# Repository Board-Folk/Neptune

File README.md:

# Neptune 32X/MD2

The Sega Neptune was an unreleased console that would have been a stand-alone 32X.
This project provides a PCB that combines the 32X and Mega Drive/Genesis 2 that fits
in an original Mega Drive/Genesis 2 case or the reimagined Neptune case designed by
DVIZIX.

[![Promo video][PromoVideoThumbnail]][PromoVideo]

**NOTE**: In order to use these PCBs successfully you will need to be proficient in:

* Soldering-fine pitched surface mount components.
* In most cases, desoldering said components to obtain these from a donor board.
* Troubleshooting any issues that may arise.

Development and testing of these PCBs has shown that successfully assembling a
working board is challenging even for skilled, experienced builders. Please read the
build notes below carefully before starting. If you are in any doubt, it is highly
recommended to enlist the help of someone with a known track record.

The authors are not obliged to provide support, nor shall they be held responsible
for botched attempts at using these boards. Should you however find a legitimate flaw
in the board's design or have suggestions for improvements, please feel free to
submit an issue.

## Errata

When using anything other than the latest release, check against this table if there
are any outstanding fixes that should be applied to your particular board revision.

| Issue          | Description                          | Affected Revisions  | Service Bulletin           |
|----------------|--------------------------------------|---------------------|----------------------------|
| [#3][Issue3]   | Region/version register instability. | <= r1.3 (Sept 2024) | [CSB_NEP_001][CSB_NEP_001] |
| -              | Black screen after power-on reset.   | <= r1.3 (Sept 2024) | [CSB_NEP_002][CSB_NEP_002] |

[Issue3]: https://github.com/Board-Folk/Neptune/issues/3
[CSB_NEP_001]: https://raw.githubusercontent.com/Board-Folk/Neptune/master/service/CSB_NEP_001.pdf
[CSB_NEP_002]: https://raw.githubusercontent.com/Board-Folk/Neptune/master/service/CSB_NEP_002.pdf

## Features and Limitations

* Fits original Mega Drive 2 (PAL), Genesis 2 or DVIZIX Neptune cases. Separate
  power/reset switch locations are provided for each (see the `stl` directory for
  files with which to 3D print spacers for the buttons if using the DVIZIX case).
* NOT compatible with the Japanese Mega Drive 2 case due to this using a sliding
  power switch with a different footprint to that of the push button style.
* Modern power circuit by Zaxour (requires 9V DC PSU rated for at least 1A).
* Integrated switchless region mod using PIC16F630 or compatible.
* Integrated "Triple Bypass" mod for improved RGB and audio.
* Provisional support for Sega Master System games via integrated mod by DogP.\*
* Compatible with the original Sega CD/Mega CD.\*\*
* Not compatible with flash cart-based Sega CD/Mega CD implementations such as
  the Mega EverDrive Pro. The Mega SD does how ever work when used in combination
  with the MSDEXP expansion port adapter (thanks to Bob from [RetroRGB](https://www.retrorgb.com/)
  for [testing this live][RetroRGBCDVideo]).
* As the 32X hardware is integrated into the design, there is NO way to disable this.
* No mono audio output.
* No Dual Frequency Oscillator (DFO) is built in but, should you opt to install
  one that fits in the original oscillator footprint, a pad for the PAL/NTSC
  switching signal is provided close by.

\* Master System compatibility is not extensively tested. Original cartridges have
been shown to work when using simple pass-through adapters. Using Mega Drive flash
carts to run Master System games may or may not work. Some such cartridges check for
the presence of a 32X and, if detected, will refuse to boot in Master System mode,
as this would usually cause a hardware conflict. In some cases this check can be
disabled in the flash cart's menu. While we believe that this is safe, you do so at
your own risk.

\*\* The model 2 Sega CD/Mega CD uses the +9V pin on the expansion connector to power
itself on along with the attached console. This board does not however provide 9V
to this pin. Testing has shown that the CD hardware will also power on with only 5V
on this pin. We're not aware of any add-ons that require 9V on the expansion connector,
so what would usually be +9V is connected to +5V by a trace between the pads near
B26 and B28. If you do however really need it, there is another +9V pad near the
power jack. This is however not switched along with the console and will remain
powered as long as there is power to the jack. You could rig up something with
a transistor or MOSFET to make 9V switch on along with the console. Of course, making
any such modification will require the trace between +5V and +9V be cut.

## PCB Production

**NOTE**: it is highly discouraged to have boards manufactured based on the current
state of the master branch or indeed any commit other than those tagged as actual
[releases][Releases]. Any other commits may contain errors or half-finished features
and using them limits the ability of others to provide support due to the unknown
state of the boards.

Minimum track widths, clearances and via sizes are within the standard
offering of modern PCB fabricators. Gerber files are generated with the relevant
options for [JLCPCB](https://jlcpcb.com/) (included in the "Assets" section of
the individual [releases][Releases]). Placeholders for the order number are
provided so remember to select the "Specify location" option for this when ordering.
If using another service you may wish to remove or replace this placeholder.
If using PCBWay, please consider using this [shared project][PCBWayProject] for
which a percentage of the order amount is credited to the author. (However, if you
really want to contribute, a less expensive PCB service and a donation via
[Ko-fi][Ko-fi] works out better for all involved!)

The design is verified to work as a 4-layer PCB with 1 oz outer and 1/2 oz inner
layers. The intended layer order is Front, In1, In2, Back. A leaded HASL finish is
adequate and ensures compatibility with the original solder that will inevitably be
left behind on salvaged parts. If you plan to use a Mega CD/Sega CD or anything that
uses the edge connector you might want to opt for an ENIG or other gold finish for
this. Chamfering of the expansion edge connector is recommended.

For independent testing of the Mega Drive side, you might like to try Chrissy's
experimental bypass boards for IC504 and IC505 in the ``helpers`` directory (more
info below in the build notes).

## Bill of Materials

For a complete BOM, consult the KiCad project itself. For assembly you may wish
to use the generated Interactive BOM but this is not as detailed (use the
`ibom.html` file in the "Assets" section of [your board's release][Releases]).

Parts are numbered according to the following scheme:

| Number  | Description                                        |
|:-------:|:---------------------------------------------------|
| < 500   | Original to Mega Drive/Genesis 2                   |
| 500-599 | Original to 32X (subtract 500 for original number) |
| >= 600  | Additional/replacement parts                       |

It is assumed that most parts will be obtained from donor Mega Drive/Genesis and
32X units. The project was initially based on a VA1 PAL Mega Drive 2 and VA1 PAL
32X. [Other Mega Drive/Genesis revisions][Revisions] may be usable if these also
use a 315-5660 or [compatible ASIC][ASICs]. Be aware that some ASICs (e.g. the
315-5660-10 variant found on some Japanese revisions) are known not to support 50
Hz operation which will limit the usefullness of the integrated switchless region
mod. If using the 315-5660-01 chip, a 1K pull-down resistor is required on the
`/SC` line, for which the footprint of the usually unused capacitor C15 provides a
convenient location. All 32X revisions should be usable but this has not yet been
confirmed. Note the differences in parts between MD and 32X revisions/regions as
documented in the schematics. It is probably not feasible to list the differences
between all possible revisions but should you work out a solution for a particular
donor board, please let us know so we can include it in this documentation.

Parts marked "\*" have different values based on region or revision, or may not be
present on some revisions, so refer to the schematic and your donor hardware.
Parts marked "PAL" on the board are supposedly only used on PAL Mega Drives. Parts
marked "VA0" and "VA1" are for those revisions of 32X only. However, should your
donor hardware have any of these parts it would seem wise to transfer them to the
new board regardless of the original region/revision. When in doubt just remember
that, when it come to original parts, in essence it is about moving the donors'
parts to the new board. If it's on the donor, use it; if it's not, then it was never
required in the first place.

If your donor 32X has a THT diode for `/VRES` on the main board, experimental
evidence suggest this does not need to be transferred. Just in case, the footprint
`D699` is provided should you require it. The footprint is however bridged, as on
other revisions there is no diode and this is simply a direct connection. If
installing the diode you will therefore need to cut the trace between the pads.
The accompanying capacitor may be installed at location `C553`.

All SMD passives on the board have 0805 or larger footprints for easier soldering.
Inductor footprints are 1210 but you can of course use narrower such as 1206.
If reusing MD2 passives, these should therefore fit well. Many 32X passives are
smaller but should still fit. If you plan to reuse them, do note that particularly
the smaller capacitors are prone to losing their metal end caps and, being so small,
this is not always immediately apparent. If you see solder balling up instead of
flowing nicely, this may well be the problem.

Tolerances of original capacitors are unknown but 20% for electrolytic and 5% for
SMD types is a good rule of thumb. If lower is available, even better. Any critical
tolerances will be specified on the schematic/BOM. Capacitor voltages are stated
where known. 0805 capacitors generally have a voltage rating of 50V or more, which
is more than sufficient.

## Build Notes

### General

* Before disassembling the donor consoles, test these thoroughly using the "Mars
  Checker" diagnostic ROM. Please note that running this from some flash carts
  (particular EverDrive models or Mega SD) may yield unreliable results. Even on
  known-good original hardware, you may be presented with a red screen when booting
  or test runs may/may not succeed seemingly at random. For this reason, it's
  recommended to run the tests several times. If you are unable to boot the
  diagnostics using your particular flash cart, consider a simpler single-image
  (i.e. no menu) one or something EPROM-based.

* Macho Nacho Productions has an [informative video][MachoNachoVideo] on the build
  process you may like to check out to get a general idea of what's required.

* The ICs on at least one side of the 32X main board (the "cartridge" part) are glued
  on making removal tricky. The glue can be softened using isopropyl alcohol, so you
  may want to give the board soak in this before starting to avoid having to use too
  much heat. Low-melt solder (e.g. ChipQuik) is very much recommended. Avoid extended
  use of hot air to avoid damaging these potentially fragile chips.

* It may sound obvious, but pay close attention to orientation when fitting ICs. The
  32X SDRAM (IC503) and some of the QFP packages have particularly subtle markings.
  It helps to mark (e.g. with tape or a groove in the package casing) pin one before
  removing the ICs from the donor boards. The legend silkscreen on the board *should*
  match that on the IC but this may not always be a reliable indicator of orientation.

* Similarly, there are two different sizes of oscillator package and the footprint has
  holes to mount either size. If using the smaller DIP-8 size, observe the correct
  location of pin 1 in the middle of the footprint and install the oscillator towards
  `IC6` as indicated by the arrows.

* Clean all boards thoroughly with e.g. isopropyl alcohol prior to starting.
  Especially HASL boards from JLC have been known to arrive with some contaminants
  present which prevent reliable solder joints. You may even like to tin the SMD
  pads and clean up with braid/wick to ensure that solder will adhere properly.

* The Triple Bypass mod features a low pass filter that can be enabled or disabled by
  fitting `R966` or `R965` respectively. As the LPF has both advantages and
  disadvantages, the choice is left to the builder. When using the provided PCB
  assembly files, the LPF is enabled by default. Otherwise, you must fit one of these
  resistors; the enable pin may not be left floating. Enabling the LPF may improve
  Mega Drive image quality at the expense of artefacts in 32X graphics. Disabling it
  may be preferable if you are using a video scaler. YMMV, so do what works for your
  particular setup.

* If using the integrated switchless mod, note that these must be programmed
  differently depending on your Neptune board's revision. For 1.5 and earlier, use
  the `switchless_xxxx.hex` files in this repo that match your LED's pinout. For
  1.6 and later, support for in-game reset functionality was added, which reassigns
  some pins of the PIC. For this reason you **must** use
  [Electroanalog's Neptune-SRB firmware][Switchless] on these boards. This later
  firmware can also be used on older boards if modified appropriately as described
  in the Neptune-SRB documentation.

* Unofficial support from experienced builders and other knowledgable individuals is
  available (on a purely voluntary basis) in [this help channel][Discord] on
  *Dubesinhower's Modding Community* Discord server.

### Order of Operations

It is possible to break down parts the build into separate steps to allow for easier
testing and troubleshooting. The following is a suggested order of operations.

* Build the power circuit (all parts in the X800 range) and test this separately.
  It should provide a steady 5V supply even without any load.

* Add the 3.3V regulator (IC510) for the 32X SDRAM and its associated capacitors.
  Check for 3.3V on the regulator output as labeled on the board.

* You may wish to install the PIC for the switchless region mod at this point as
  it should operate independently of the rest of the system. Install also the LED,
  passives in the X700 range and a temporary ~10K pull-up on `/WRES` (pin 11).
  R702 limits current through the LED and therefore determines its brightness.
  The value is based on the original MD2 LED, so you may prefer to use a higher
  value when using a modern LED, which tend to be brighter for the same current.
  If your LED has protruding "lugs" instead of just straight pins, it's recommended
  to trim these off if possible before installation to avoid damaging the board.
  Hold down the reset button to cycle through regions as indicated on the RGB LED.
  If the LED changes constantly, check pull-up `R701` is installed. The PAL/NTSC
  and JP/ENG outputs should change as appropriate. Verify that a short press of
  the button generates a `/WRES` pulse.

* If not using the switchless mod, or to bypass it for testing/troubleshooting,
  link the indicated pins and set the desired PAL/NTSC and JP/ENG values using the
  +5V and GND pads on the `IC701` footprint. Connect the LED pin of your choice to
  +5V and a single colour LED for `LED701`.

* At this point it's time to strap in and install all the MD2 components and the
  audio and video parts shared between MD and 32X. This cannot be independently
  tested without bypassing the 32X parts that usually connect to the cartridge slot.
  To this end, you may like to use the bypass flexes for IC504 and IC505 (see the
  `helpers` directory). These boards are designed to fit in place of the 32X ICs
  and simply pass the required signals directly to the Mega Drive components. If
  using the bypass boards, you will also need to temporarily connect the /YS and
  /AS signals to the cartridge slot. /YS has a labeled test point for this near
  pin B12 on the underside of the slot. /AS can be connected by bridging pins 8
  and 12 on the footprint for `IC516`. Remove these connections before installing
  the remaining 32X hardware. Note that the bypass flexes are intended to confirm
  basic functionality, i.e. that the console can boot and run code. Some strange
  behaviour or various glitches (especially related to video and audio) may be
  experienced until all components are fitted.

* When testing a newly-built Neptune, trying different kinds of cartridges and
  peripherals is useful for troubleshooting issues. Original Mega Drive cartridges
  are a good place to start as these should run even if the 32X hardware isn't
  fully operational. Running Master System cartridges via an adapter also hits
  different functionality in the MD VDP/ASIC, Z80, memory, etc. If no cartridges
  work, you may be able to boot to the BIOS screen of a Mega CD/Sega CD, which
  would point to issues around the cartridge slot and/or 32X bus multiplexing.
  Once the basic functionality is verified, diagnostics such as those in the
  [240p Test Suite][240p] and Mars Checker can be used to troubleshoot any
  remaining issues.

* For a fully assembled board WITHOUT any cables connected there should be around
  350 Ohms between VCC and ground. If you measure something wildly different this
  may indicate a short, an incorrectly installed IC or similar. With the video
  cable connected the resistance will drop to around 150 Ohms.

## Thanks/Credits

  * Zaxour for the power circuit design, invaluable support and hardware review.

  * Chrissy (@chris\_jh) for testing, support and work on making pre-assembled PCBs
    possible.

  * Leo Oliveira, Simon "Aergan" Lock, Ian (@grandoldian) and Dennis (@PointerFunction)
    for their insights, support and assistance during testing.

  * dr-goobur for diagnosing and providing the elusive fix for the mysterious "region
    flicker" issue, supported by noobguy57, angelsix, v00dooperson and many more
    behind the scenes.

  * The rest of the Board Folk for their support and general coolness.

  * Dubesinhower and the modding community members on Discord for generously supporting
    builders.

## Legal

Copyright ©2024

You are free to produce PCBs using this project's designs at your own risk, for
your own use or for sale and/or repair at a reasonable price. Attribution is
appreciated. Publishing files for PCB production (such as, but not limited to,
Gerber files) for financial compensation (sales commission, credit, etc.) on for
example "shared project"-style websites or similar is prohibited.

Derivative works must be released under similar Open Source terms such that all
sources are publicly available. The original authors' names and copyright statements
may not be removed.

The authors are not obliged to provide support of any kind. Under no circumstances
shall the authors be held responsible or liable in any way for losses, damages or
costs resulting from the use of the information and/or resources of this project.

The resources are provided "as-is" without warranty of any kind, either
expressed or implied, including, but not limited to, the implied warranties
of merchantability and fitness for a particular purpose.

[Releases]: https://github.com/Board-Folk/Neptune/releases
[Switchless]: https://github.com/Electroanalog/Neptune-SRB
[Revisions]: https://segaretro.org/Sega_Mega_Drive/Hardware_revisions
[ASICs]: https://consolemods.org/wiki/Genesis:ASIC_Information
[240p]: https://junkerhq.net/xrgb/index.php?title=240p_test_suite
[MachoNachoVideo]: https://youtu.be/PcP60-0NIEw
[Discord]: https://discord.com/channels/762433496878547005/1508890749356343466
[PromoVideo]: https://youtu.be/aF1uoOP9WqM
[PromoVideoThumbnail]: https://raw.githubusercontent.com/Board-Folk/Neptune/master/img/neptune_thumbnail_play.jpg
[RetroRGBCDVideo]: https://youtube.com/live/Pf0_TwquWg0
[PCBWayProject]: https://www.pcbway.com/project/shareproject/Neptune_console_f136d0e3.html
[Ko-fi]: https://ko-fi.com/cosam

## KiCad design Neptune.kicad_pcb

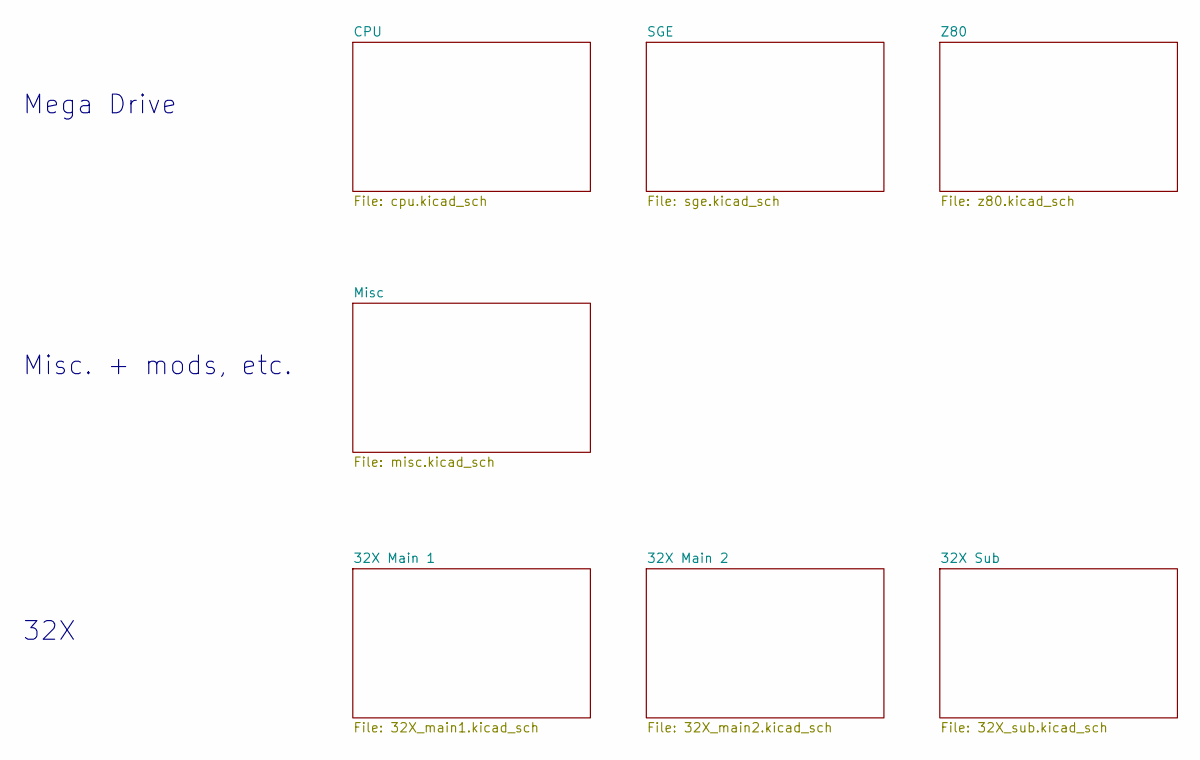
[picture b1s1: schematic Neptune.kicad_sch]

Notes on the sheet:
32X
Misc. + mods, etc.
Mega Drive

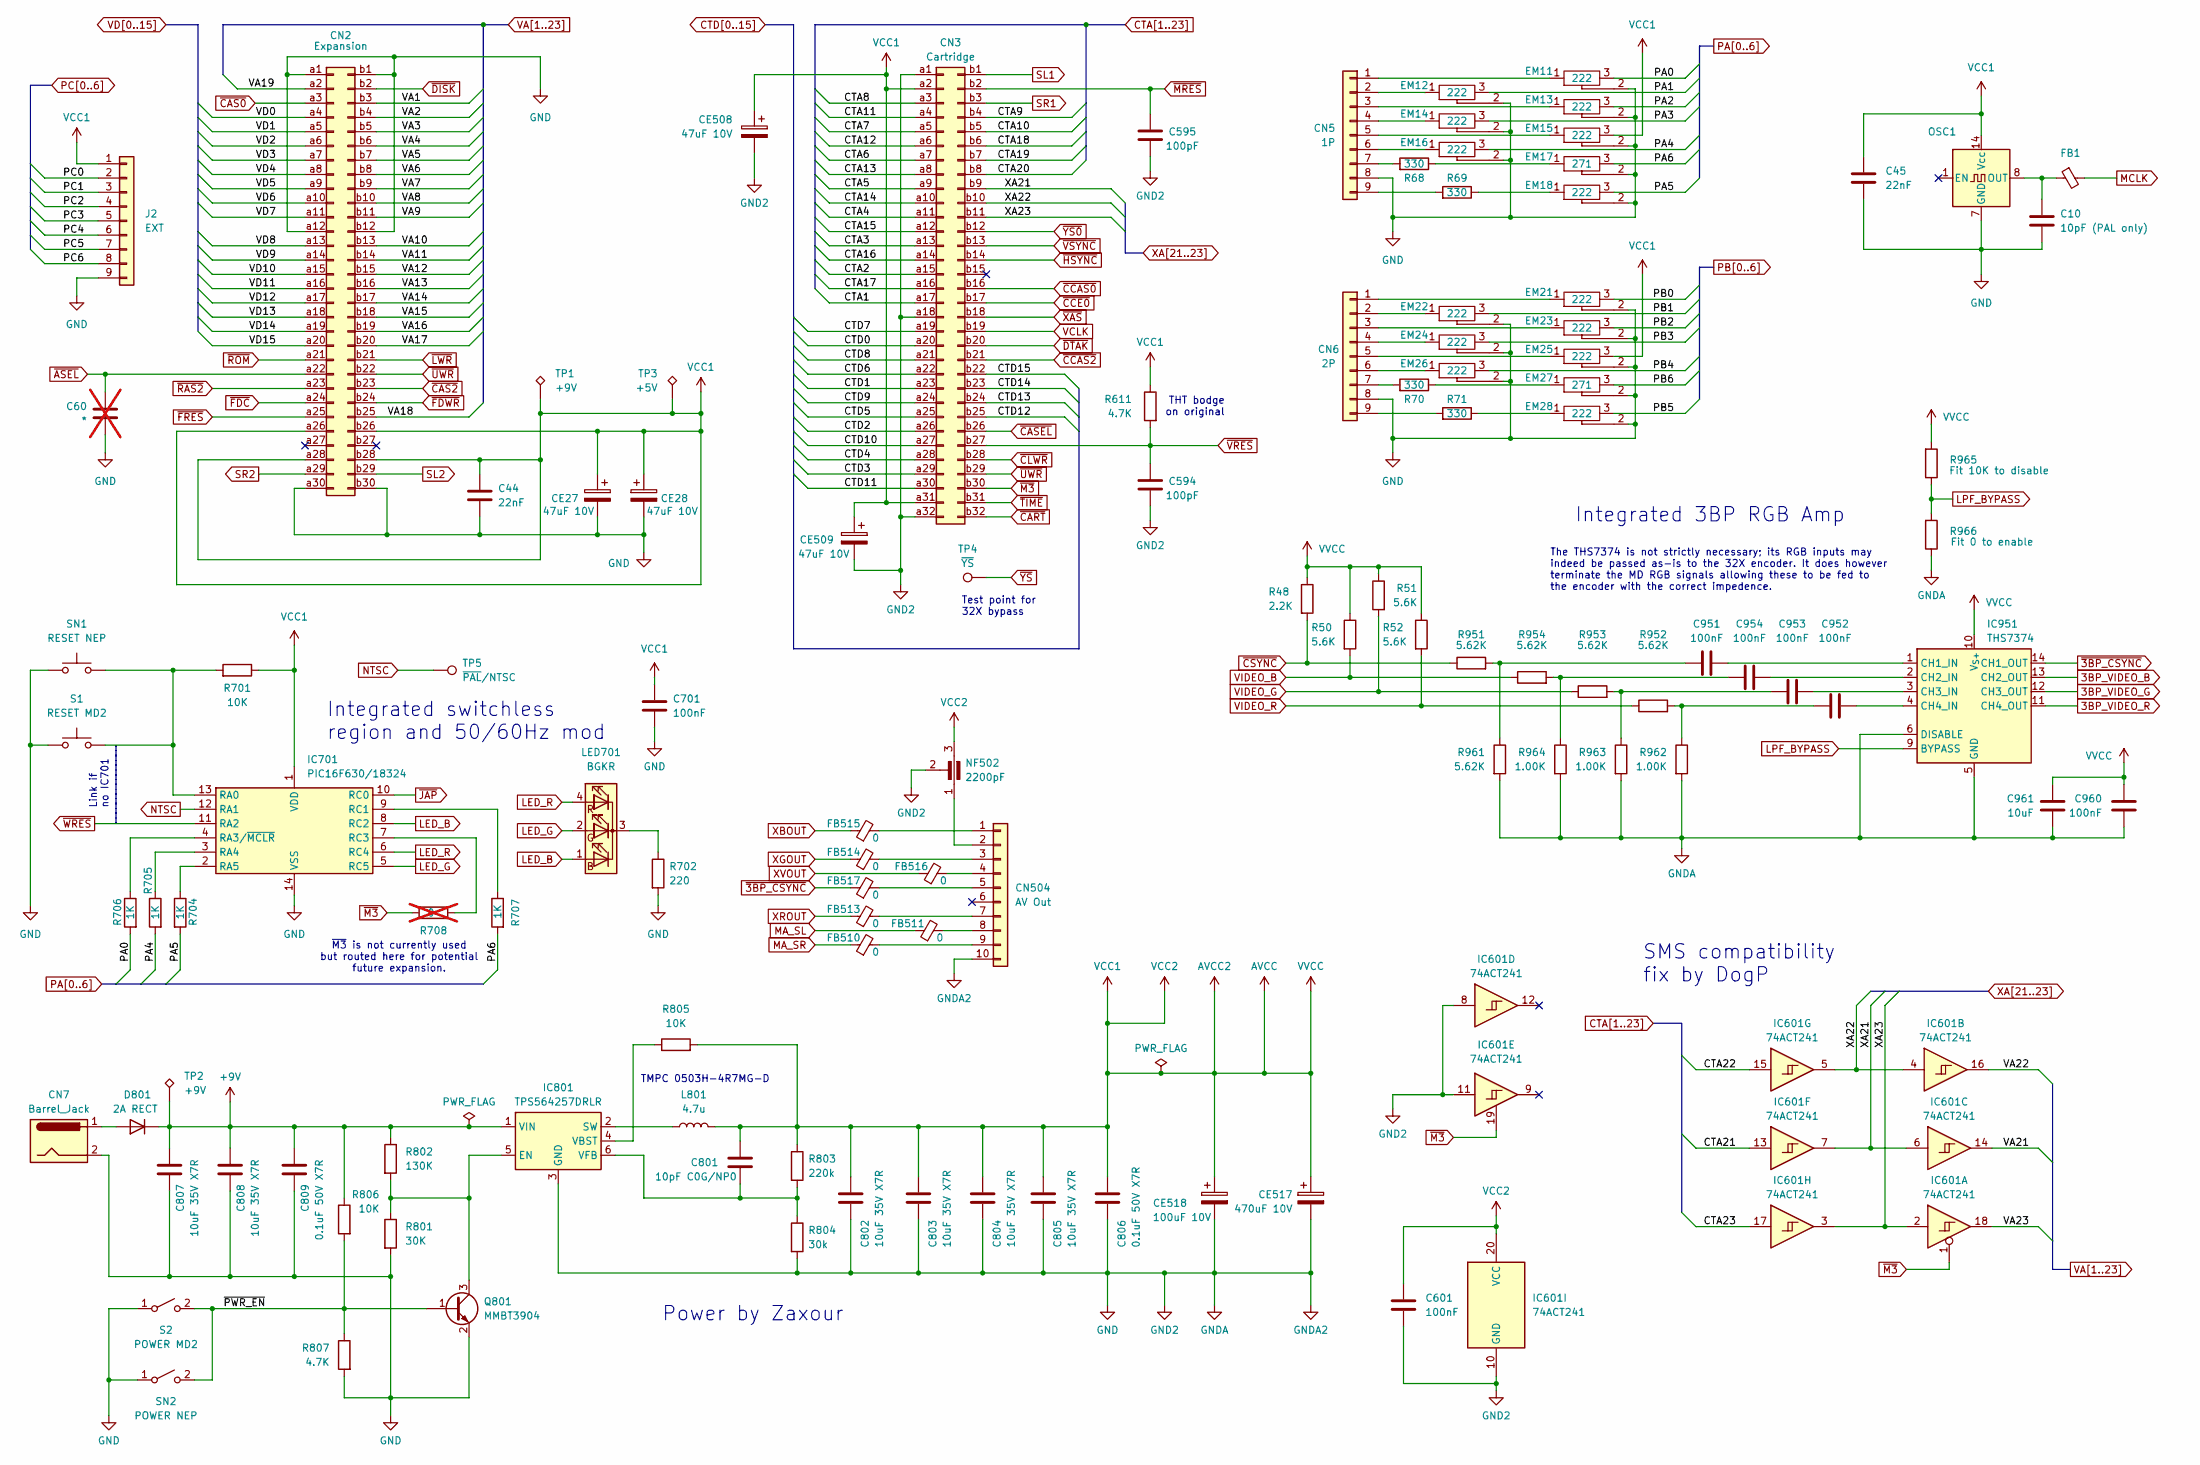
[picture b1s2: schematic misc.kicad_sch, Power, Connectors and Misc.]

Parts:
C10: 10pF (PAL only); C_0805_2012Metric; MPN VJ0805A100FXJCW1BC; LCSC Part # C520053
C44, C45: 22nF; C_0805_2012Metric; MPN VJ0805Y223JXJPW1BC; LCSC Part # C520037
C60: *; C_0805_2012Metric; MPN VJ0805A151FXJCW1BC; LCSC Part # C107111; not fitted
C594, C595: 100pF; C_0805_2012Metric; MPN VJ0805A101FXJPW1BC; LCSC Part # C1854109
C601, C701, C951, C952, C953, C954, C960: 100nF; C_0805_2012Metric; MPN VJ0805Y104JXJMT; LCSC Part # C111492
C801: 10pF C0G/NP0; C_0805_2012Metric; MPN VJ0805D100FXAAP; DigiKey 311-4160-1-ND
C802, C803, C804, C805, C807, C808: 10uF 35V X7R; C_1206_3216Metric; MPN C3216X7R1V106KT000E; DigiKey 1276-3103-1-ND
C806: 0.1uF 50V X7R; C_0805_2012Metric; MPN VJ0805Y104JFAAR; LCSC Part # C111492
C809: 0.1uF 50V X7R; C_0805_2012Metric; MPN VJ0805Y104JFAAR; DigiKey 1276-1099-1-ND
C961: 10uF; C_0805_2012Metric; MPN CGA4J1X5R1C106KT0Y0E; DigiKey 1276-1096-1-ND
CE27, CE28, CE508: 47uF 10V; CP_Radial_D5.0mm_P2.50mm; DigiKey 493-13447-1-ND
CE509: 47uF 10V; CP_Radial_D5.0mm_P2.50mm_Horizontal; DigiKey 493-13447-1-ND
CE517: 470uF 10V; CP_Radial_D8.0mm_P5.00mm
CE518: 100uF 10V; CP_Radial_D5.0mm_P2.50mm
CN2: Expansion; Edge-60P
CN3: Cartridge; Cartidge_Slot
CN5: 1P; DSUB-9
CN6: 2P; DSUB-9
CN7: Barrel_Jack; Power_Jack
CN504: AV Out; AV_Connector
D801: 2A RECT; D_SOD-128; MPN CMS06(TE12L,Q,M); LCSC Part # C261920
EM11, EM12, EM13, EM14, EM15, EM16, EM18, EM21, EM22, EM23, EM24, EM25, EM26, EM28: 222; EMI_3P
EM17, EM27: 271; EMI_3P
FB1, FB510, FB511, FB513, FB514, FB515, FB516, FB517: 0; L_0805_2012Metric; MPN CBG201209U000T; LCSC Part # C91037
IC601: 74ACT241; TSSOP-20_4.4x6.5mm_P0.65mm; MPN SN74ACT241PW; DigiKey 296-4384-1-ND
IC701: PIC16F630/18324; DIP-14_W7.62mm_Socket
IC801: TPS564257DRLR; SOT-563; MPN TPS564257DRLR; DigiKey 296-TPS564257DRLRCT-ND
IC951: THS7374; TSSOP-14_4.4x5mm_P0.65mm; MPN THS7374IPWR; LCSC Part # C2652746
J2: EXT; EXT_Breakout
L801: 4.7u; L_Murata_LQH55DN_5.7x5.0mm; MPN LQH55DN4R7M03L; DigiKey 490-9760-1-ND
LED701: BGKR; RGB_LED
NF502: 2200pF; EMI_3P
OSC1: CXO_DIP14; Oscillator_DIP-8-14
Q801: MMBT3904; SOT-23; MPN MMBT3904-TP; DigiKey MMBT3904TPMSCT-ND
R48: 2.2K; R_0805_2012Metric; MPN CRCW08052K20JNEA; DigiKey P2.20KCCT-ND
R50, R51, R52: 5.6K; R_0805_2012Metric; MPN CRCW08055K60FKEA; LCSC Part # C844634
R68, R69, R70, R71: 330; R_0805_2012Metric; MPN CRCW0805330RFKEA; LCSC Part # C844839
R611: 4.7K; R_0805_2012Metric; MPN CRCW08054K70JNEAC; DigiKey P2.20KCCT-ND
R701: 10K; R_0805_2012Metric; MPN CRCW080510K0FKEA; DigiKey P220CCT-ND
R702: 220; R_0805_2012Metric; MPN CRCW0805220RFKEAC; DigiKey P220CCT-ND
R704, R705, R706, R707: 1K; R_0805_2012Metric; MPN CRCW080510K0FKEA; DigiKey P220CCT-ND
R708: 0; R_0805_2012Metric; MPN CRCW080510K0FKEA; DigiKey P220CCT-ND; not fitted
R801: 30K; R_0805_2012Metric; MPN CRCW080530K0FKEA; DigiKey P30.0KCCT-ND
R802: 130K; R_0805_2012Metric; MPN RCS0805130KFKEA; DigiKey P162KCCT-ND
R803: 220k; R_0805_2012Metric; MPN CRCW0805220KJNEA; DigiKey P220KCCT-ND
R804: 30k; R_0805_2012Metric; MPN CRCW080530K0FKEA; DigiKey P30.0KCCT-ND
R805, R806: 10K; R_0805_2012Metric; MPN CRCW080510K0FKEA; LCSC Part # C844937
R807: 4.7K; R_0805_2012Metric; MPN CRCW08054K70JNEAC; LCSC Part # C2077067
R951, R952, R953, R954, R961: 5.62K; R_0805_2012Metric; MPN TNPW08055K62FHEA\; DigiKey P5.62KCCT-ND
R962, R963, R964: 1.00K; R_0805_2012Metric; MPN CRCW08051K00FKEA; DigiKey P1.00KCCT-ND
R965: Fit 10K to disable; R_0805_2012Metric; DigiKey P5.62KCCT-ND
R966: Fit 0 to enable; R_0805_2012Metric; DigiKey P5.62KCCT-ND
S1: RESET MD2; Reset_Switch
S2: POWER MD2; Power_Switch
SN1: RESET NEP; Reset_Switch
SN2: POWER NEP; Power_Switch
TP1, TP2: +9V; PinHeader_1x01_P2.54mm_Vertical
TP3: +5V; PinHeader_1x01_P2.54mm_Vertical
TP4: ~{YS}; TestPoint_Pad_D1.5mm
TP5: ~{PAL}/NTSC; TestPoint_Pad_D1.5mm

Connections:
3BP_VIDEO_B: IC951.13 (CH2_OUT); also elsewhere on the board
3BP_VIDEO_G: IC951.12 (CH3_OUT); also elsewhere on the board
3BP_VIDEO_R: IC951.11 (CH4_OUT); also elsewhere on the board
+9V: C807.1, C808.1, C809.1, D801.1 (K), IC801.1 (VIN), R802.1, R806.1, TP2.1
/Misc/~PWR_EN: Q801.1 (B), R806.2, R807.1, S2.2 (B), SN2.2 (B)
AVCC: C45.1, C601.1, C701.1, C801.1, C802.1, C803.1, C804.1, C805.1, C806.1, C960.1, C961.2, CE27.1, CE28.1, CE508.1, CE509.1, CE517.1, CE518.1, CN2.a26, CN2.a28, CN2.b26, CN2.b28, CN3.a2, CN3.a31, EM15.3, EM25.3, IC601.20 (VCC), IC701.1 (VDD), IC951.10 (V_{S+}), J2.1, L801.2, NF502.3, OSC1.14 (Vcc), R48.1, R50.1, R51.1, R52.1, R611.1, R701.1, R803.1, R805.2, R965.2, TP1.1, TP3.1; also elsewhere on the board
CTA1: CN3.a17; also elsewhere on the board
CTA2: CN3.a15; also elsewhere on the board
CTA3: CN3.a13; also elsewhere on the board
CTA4: CN3.a11; also elsewhere on the board
CTA5: CN3.a9; also elsewhere on the board
CTA6: CN3.a7; also elsewhere on the board
CTA7: CN3.a5; also elsewhere on the board
CTA8: CN3.a3; also elsewhere on the board
CTA9: CN3.b4; also elsewhere on the board
CTA10: CN3.b5; also elsewhere on the board
CTA11: CN3.a4; also elsewhere on the board
CTA12: CN3.a6; also elsewhere on the board
CTA13: CN3.a8; also elsewhere on the board
CTA14: CN3.a10; also elsewhere on the board
CTA15: CN3.a12; also elsewhere on the board
CTA16: CN3.a14; also elsewhere on the board
CTA17: CN3.a16; also elsewhere on the board
CTA18: CN3.b6; also elsewhere on the board
CTA19: CN3.b7; also elsewhere on the board
CTA20: CN3.b8; also elsewhere on the board
CTA21: IC601.13; also elsewhere on the board
CTA22: IC601.15; also elsewhere on the board
CTA23: IC601.17; also elsewhere on the board
CTD0: CN3.a20; also elsewhere on the board
CTD1: CN3.a23; also elsewhere on the board
CTD2: CN3.a26; also elsewhere on the board
CTD3: CN3.a29; also elsewhere on the board
CTD4: CN3.a28; also elsewhere on the board
CTD5: CN3.a25; also elsewhere on the board
CTD6: CN3.a22; also elsewhere on the board
CTD7: CN3.a19; also elsewhere on the board
CTD8: CN3.a21; also elsewhere on the board
CTD9: CN3.a24; also elsewhere on the board
CTD10: CN3.a27; also elsewhere on the board
CTD11: CN3.a30; also elsewhere on the board
CTD12: CN3.b25; also elsewhere on the board
CTD13: CN3.b24; also elsewhere on the board
CTD14: CN3.b23; also elsewhere on the board
CTD15: CN3.b22; also elsewhere on the board
GND: C10.2, C44.2, C45.2, C60.2, C594.1, C595.1, C601.2, C701.2, C802.2, C803.2, C804.2, C805.2, C806.2, C807.2, C808.2, C809.2, C960.2, C961.1, CE27.2, CE28.2, CE508.2, CE509.2, CE517.2, CE518.2, CN2.a1, CN2.a12, CN2.a30, CN2.b1, CN2.b12, CN2.b30, CN3.a1, CN3.a18, CN3.a32, CN5.8, CN6.8, CN7.2, CN504.10, EM11.2, EM12.2, EM13.2, EM14.2, EM15.2, EM16.2, EM17.2, EM18.2, EM21.2, EM22.2, EM23.2, EM24.2, EM25.2, EM26.2, EM27.2, EM28.2, IC601.8, IC601.10 (GND), IC601.11, IC701.14 (VSS), IC801.3 (GND), IC951.5 (GND), IC951.6 (DISABLE), J2.9, NF502.2, OSC1.7 (GND), Q801.2 (E), R702.2, R801.2, R804.2, R807.2, R961.2, R962.2, R963.2, R964.2, R966.1, S1.1, S2.1 (A), SN1.1, SN2.1 (A); also elsewhere on the board
LED_B: IC701.8 (RC2), LED701.1 (BA)
LED_G: IC701.5 (RC5), LED701.2 (GA)
LED_R: IC701.6 (RC4), LED701.4 (RA)
LPF_BYPASS: IC951.9 (BYPASS), R965.1, R966.2
MA_SL: FB511.1; also elsewhere on the board
MA_SR: FB510.1; also elsewhere on the board
MCLK: FB1.2; also elsewhere on the board
NTSC: IC701.12 (RA1), TP5.1; also elsewhere on the board
unnamed: C951.1, R951.2, R961.1
unnamed: C952.1, R952.2, R962.1
unnamed: C953.1, R953.2, R963.1
unnamed: C954.1, R954.2, R964.1
unnamed: CN5.1, EM11.1
unnamed: CN5.2, EM12.1
unnamed: CN5.3, EM13.1
unnamed: CN5.4, EM14.1
unnamed: CN5.5, EM15.1
unnamed: CN5.6, EM16.1
unnamed: CN5.7, R68.2
unnamed: CN5.9, R69.2
unnamed: CN6.1, EM21.1
unnamed: CN6.2, EM22.1
unnamed: CN6.3, EM23.1
unnamed: CN6.4, EM24.1
unnamed: CN6.5, EM25.1
unnamed: CN6.6, EM26.1
unnamed: CN6.7, R70.2
unnamed: CN6.9, R71.2
unnamed: CN504.1, FB515.2
unnamed: CN504.2, NF502.1
unnamed: CN504.3, FB514.2
unnamed: CN504.4, FB516.2
unnamed: CN504.5, FB517.2
unnamed: CN504.7, FB513.2
unnamed: CN504.8, FB511.2
unnamed: CN504.9, FB510.2
unnamed: CN7.1, D801.2 (A)
unnamed: EM17.1, R68.1
unnamed: EM18.1, R69.1
unnamed: EM27.1, R70.1
unnamed: EM28.1, R71.1
unnamed: IC701.13 (RA0), R701.2, S1.2, SN1.2
unnamed: IC701.4 (RA3/~MCLR), R706.1
unnamed: IC701.3 (RA4), R705.1
unnamed: IC701.2 (RA5), R704.1
unnamed: IC701.9 (RC1), R707.1
unnamed: IC701.7 (RC3), R708.1
unnamed: IC801.5 (EN), Q801.3 (C), R801.1, R802.2
unnamed: IC801.2 (SW), L801.1
unnamed: IC801.4 (VBST), R805.1
unnamed: C801.2, IC801.6 (VFB), R803.2, R804.1
unnamed: C951.2, IC951.1 (CH1_IN)
unnamed: C954.2, IC951.2 (CH2_IN)
unnamed: C953.2, IC951.3 (CH3_IN)
unnamed: C952.2, IC951.4 (CH4_IN)
unnamed: LED701.3 (K), R702.1
unnamed: C10.1, FB1.1, OSC1.8 (OUT)
PA0: EM11.3, R706.2; also elsewhere on the board
PA1: EM12.3; also elsewhere on the board
PA2: EM13.3; also elsewhere on the board
PA3: EM14.3; also elsewhere on the board
PA4: EM16.3, R705.2; also elsewhere on the board
PA5: EM18.3, R704.2; also elsewhere on the board
PA6: EM17.3, R707.2; also elsewhere on the board
PB0: EM21.3; also elsewhere on the board
PB1: EM22.3; also elsewhere on the board
PB2: EM23.3; also elsewhere on the board
PB3: EM24.3; also elsewhere on the board
PB4: EM26.3; also elsewhere on the board
PB5: EM28.3; also elsewhere on the board
PB6: EM27.3; also elsewhere on the board
PC0: J2.2; also elsewhere on the board
PC1: J2.3; also elsewhere on the board
PC2: J2.4; also elsewhere on the board
PC3: J2.5; also elsewhere on the board
PC4: J2.6; also elsewhere on the board
PC5: J2.7; also elsewhere on the board
PC6: J2.8; also elsewhere on the board
SL1: CN3.b1; also elsewhere on the board
SL2: CN2.b29; also elsewhere on the board
SR1: CN3.b3; also elsewhere on the board
SR2: CN2.a29; also elsewhere on the board
VA1: CN2.b3; also elsewhere on the board
VA2: CN2.b4; also elsewhere on the board
VA3: CN2.b5; also elsewhere on the board
VA4: CN2.b6; also elsewhere on the board
VA5: CN2.b7; also elsewhere on the board
VA6: CN2.b8; also elsewhere on the board
VA7: CN2.b9; also elsewhere on the board
VA8: CN2.b10; also elsewhere on the board
VA9: CN2.b11; also elsewhere on the board
VA10: CN2.b13; also elsewhere on the board
VA11: CN2.b14; also elsewhere on the board
VA12: CN2.b15; also elsewhere on the board
VA13: CN2.b16; also elsewhere on the board
VA14: CN2.b17; also elsewhere on the board
VA15: CN2.b18; also elsewhere on the board
VA16: CN2.b19; also elsewhere on the board
VA17: CN2.b20; also elsewhere on the board
VA18: CN2.b25; also elsewhere on the board
VA19: CN2.a2; also elsewhere on the board
VA21: IC601.14; also elsewhere on the board
VA22: IC601.16; also elsewhere on the board
VA23: IC601.18; also elsewhere on the board
VCLK: CN3.b19; also elsewhere on the board
VD0: CN2.a4; also elsewhere on the board
VD1: CN2.a5; also elsewhere on the board
VD2: CN2.a6; also elsewhere on the board
VD3: CN2.a7; also elsewhere on the board
VD4: CN2.a8; also elsewhere on the board
VD5: CN2.a9; also elsewhere on the board
VD6: CN2.a10; also elsewhere on the board
VD7: CN2.a11; also elsewhere on the board
VD8: CN2.a13; also elsewhere on the board
VD9: CN2.a14; also elsewhere on the board
VD10: CN2.a15; also elsewhere on the board
VD11: CN2.a16; also elsewhere on the board
VD12: CN2.a17; also elsewhere on the board
VD13: CN2.a18; also elsewhere on the board
VD14: CN2.a19; also elsewhere on the board
VD15: CN2.a20; also elsewhere on the board
VIDEO_B: R50.2, R954.1; also elsewhere on the board
VIDEO_G: R51.2, R953.1; also elsewhere on the board
VIDEO_R: R52.2, R952.1; also elsewhere on the board
XA21: CN3.b9, IC601.6, IC601.7
XA22: CN3.b10, IC601.4, IC601.5
XA23: CN3.b11, IC601.2, IC601.3
XBOUT: FB515.1; also elsewhere on the board
XGOUT: FB514.1; also elsewhere on the board
XROUT: FB513.1; also elsewhere on the board
XVOUT: FB516.1; also elsewhere on the board
~3BP_CSYNC: FB517.1, IC951.14 (CH1_OUT); also elsewhere on the board
~ASEL: C60.1, CN2.a22; also elsewhere on the board
~CART: CN3.b32; also elsewhere on the board
~CAS0: CN2.a3; also elsewhere on the board
~CAS2: CN2.b23; also elsewhere on the board
~CASEL: CN3.b26; also elsewhere on the board
~CCAS0: CN3.b16; also elsewhere on the board
~CCAS2: CN3.b21; also elsewhere on the board
~CCE0: CN3.b17; also elsewhere on the board
~CLWR: CN3.b28; also elsewhere on the board
~CSYNC: R48.2, R951.1; also elsewhere on the board
~DISK: CN2.b2; also elsewhere on the board
~DTAK: CN3.b20; also elsewhere on the board
~FDC: CN2.a24; also elsewhere on the board
~FDWR: CN2.b24; also elsewhere on the board
~FRES: CN2.a25; also elsewhere on the board
~HSYNC: CN3.b14; also elsewhere on the board
~JAP: IC701.10 (RC0); also elsewhere on the board
~LWR: CN2.b21; also elsewhere on the board
~M3: CN3.b30, IC601.1, IC601.19, R708.2; also elsewhere on the board
~MRES: C595.2, CN3.b2; also elsewhere on the board
~RAS2: CN2.a23; also elsewhere on the board
~ROM: CN2.a21; also elsewhere on the board
~TIME: CN3.b31; also elsewhere on the board
~UWR: CN2.b22, CN3.b29; also elsewhere on the board
~VRES: C594.2, CN3.b27, R611.2; also elsewhere on the board
~VSYNC: CN3.b13; also elsewhere on the board
~WRES: IC701.11 (RA2); also elsewhere on the board
~XAS: CN3.b18; also elsewhere on the board
~YS0: CN3.b12; also elsewhere on the board
~YS: TP4.1; also elsewhere on the board

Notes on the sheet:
TMPC 0503H-4R7MG-D
Power by Zaxour
THT bodge on original
~{M3} is not currently used but routed here for potential future expansion.
Test point for 32X bypass
SMS compatibility fix by DogP
Link if no IC701
Integrated switchless region and 50/60Hz mod
Integrated 3BP RGB Amp
The THS7374 is not strictly necessary; its RGB inputs may indeed be passed as-is to the 32X encoder. It does however terminate the MD RGB signals allowing these to be fed to the encoder with the correct impedence.

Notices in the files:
Neptune.kicad_pcb:
https://github.com/Board-Folk/Neptune ©2025-2026
